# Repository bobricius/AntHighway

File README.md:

# AntHighway
https://hackaday.io/project/164821-ant-highway-linear-motor-for-micro-cars

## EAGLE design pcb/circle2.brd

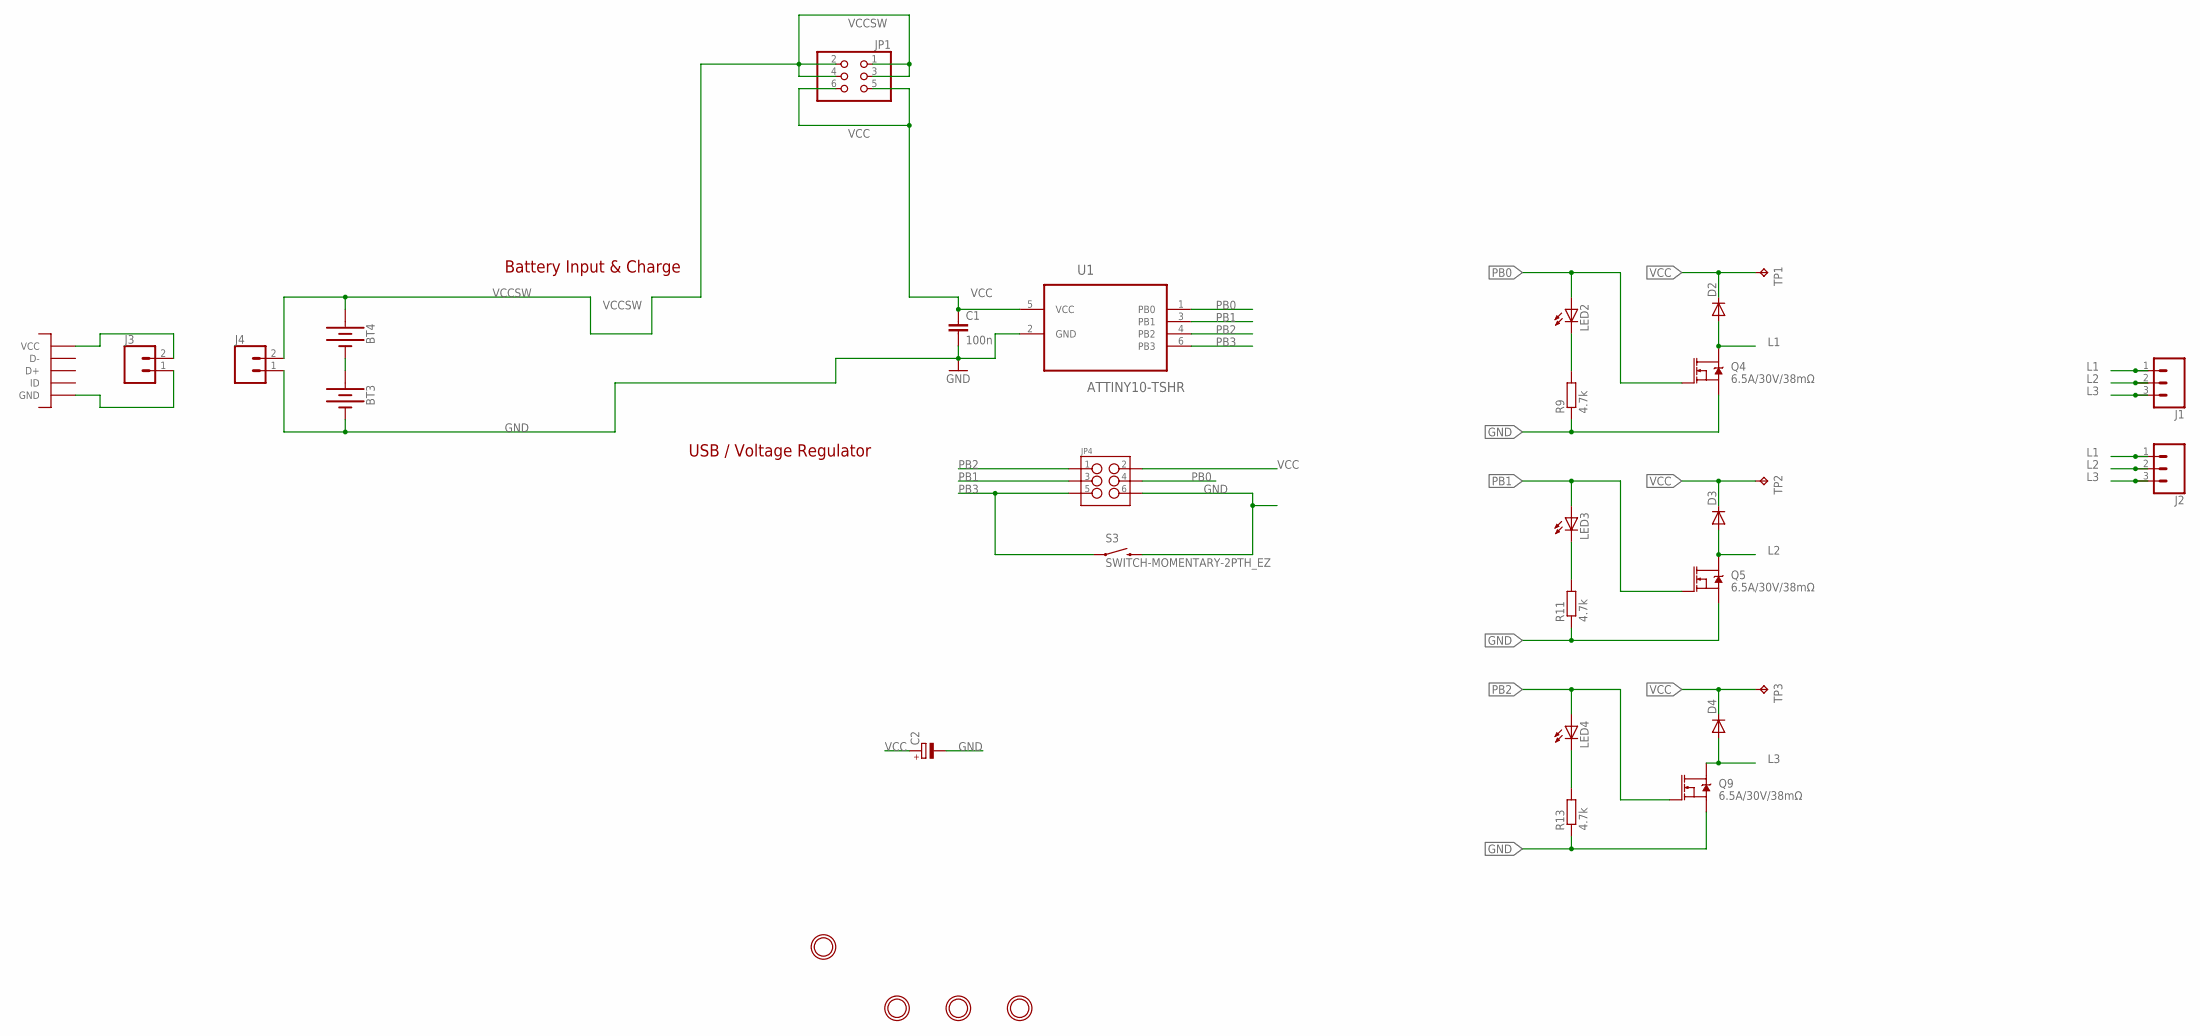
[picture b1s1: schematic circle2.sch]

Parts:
BT3, BT4: BATTERY-AA_KIT; BATTERY-AA-KIT
C1: 100n; 0805
C2: CPOL-EUA; PANASONIC_A
D2, D3, D4: DIODE-DO214AC; DO214AC
J1, J2: CONN_031X03_NO_SILK; 1X03_NO_SILK
J3, J4: CONN_02LOCK_LONGPADS; 1X02_LOCK_LONGPADS
JP1: PINHD-2X3; 2X03
JP4: M03X2NO_SILK; 2X3-NS
LED2, LED3, LED4: LEDKA-3528ASYC; KA-3528ASYC
Q4, Q5, Q9: 6.5A/30V/38mΩ; SO08
R9, R11, R13: 4.7k; R0603
S3: SWITCH-MOMENTARY-2PTH_EZ; TACTILE-PTH-EZ
TP1, TP2, TP3: TPTP20SQ; TP20SQ
U1: ATTINY10-TSHR; SOT95P280X145-6N
U$1, U$2, U$3, U$7: MOUNTINGHOLE2.0; MOUNTINGHOLE_2.0_PLATED
U$5: MICROUSB; MICRO_B

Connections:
GND: BT3.GND@1 (-), C1.2, C2.-, J4.1, JP4.6, Q4.1 (S), Q4.2 (S), Q4.3 (S), Q5.1 (S), Q5.2 (S), Q5.3 (S), Q9.1 (S), Q9.2 (S), Q9.3 (S), R9.1, R11.1, R13.1, S3.3 (2), U1.2 (GND)
GND1: J3.1, U$5.GND1 (GND), U$5.GND2 (GND), U$5.GND3 (GND), U$5.GND4 (GND), U$5.GND7 (GND), U$5.GND8 (GND), U$5.P5 (GND)
L1: D2.A, J1.1, J2.1, Q4.5 (D), Q4.6 (D), Q4.7 (D), Q4.8 (D)
L2: D3.A, J1.2, J2.2, Q5.5 (D), Q5.6 (D), Q5.7 (D), Q5.8 (D)
L3: D4.A, J1.3, J2.3, Q9.5 (D), Q9.6 (D), Q9.7 (D), Q9.8 (D)
unnamed: BT3.PWR@1 (+), BT4.GND@1 (-)
unnamed: LED2.C, R9.2
unnamed: LED3.C, R11.2
unnamed: LED4.C, R13.2
PB0: JP4.4, LED2.A, Q4.4 (G), U1.1 (PB0)
PB1: JP4.3, LED3.A, Q5.4 (G), U1.3 (PB1)
PB2: JP4.1, LED4.A, Q9.4 (G), U1.4 (PB2)
PB3: JP4.5, S3.1, U1.6 (PB3)
VCC: C1.1, C2.+, D2.C, D3.C, D4.C, JP1.5, JP1.6, JP4.2, TP1.TP, TP2.TP, TP3.TP, U1.5 (VCC)
VCC1: J3.2, U$5.P1 (VCC)
VCCSW: BT4.PWR@1 (+), J4.2, JP1.1, JP1.2, JP1.3, JP1.4

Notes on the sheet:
USB / Voltage Regulator
Battery Input & Charge

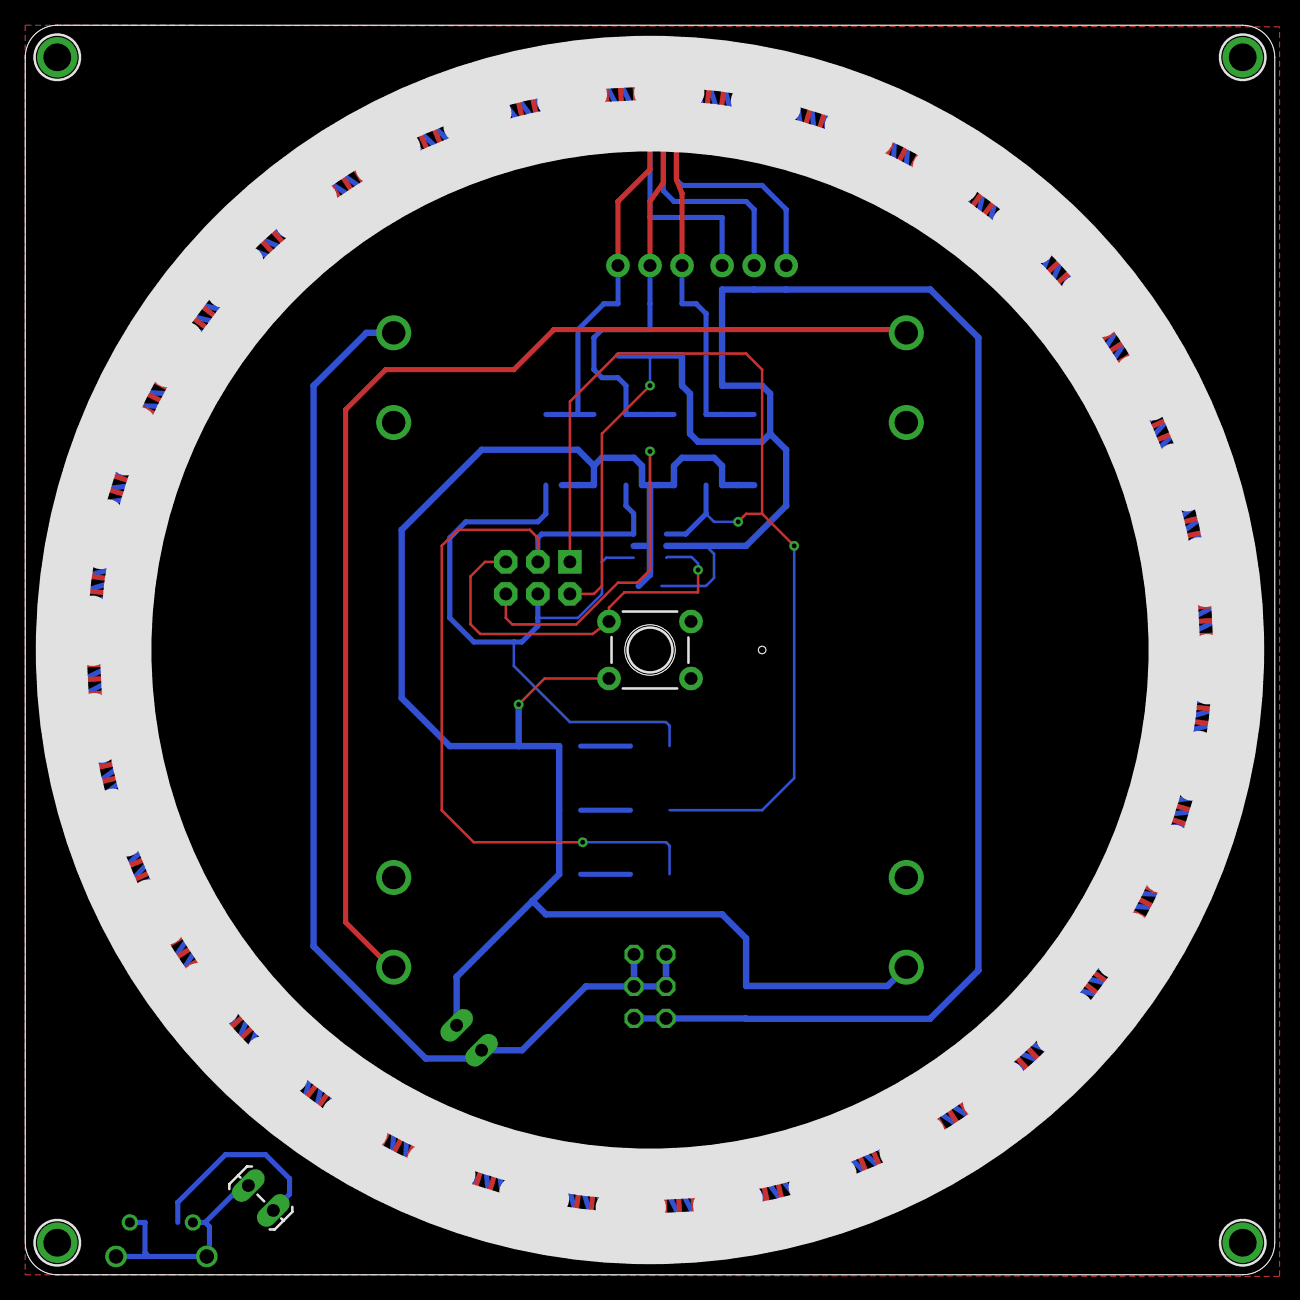
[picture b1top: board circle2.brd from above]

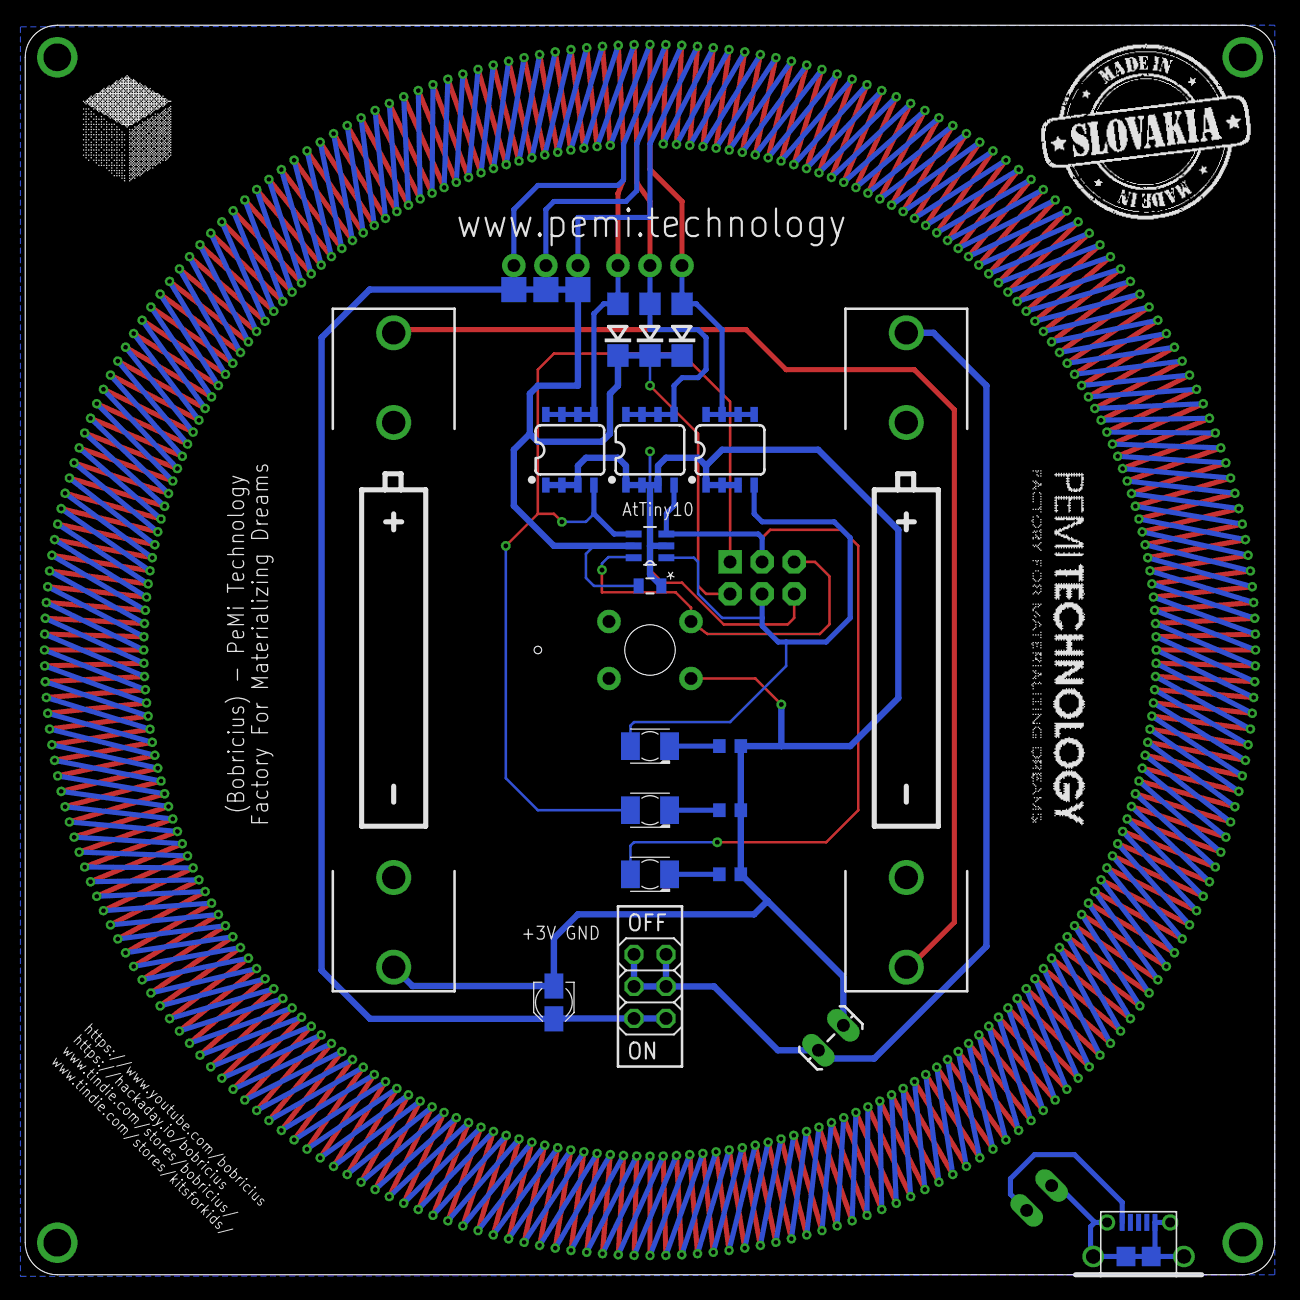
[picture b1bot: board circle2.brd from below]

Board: 2 copper layers, 99.1 x 99.1 mm, 32 parts (23 on the bottom side), 16 nets.

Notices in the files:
parts and their libraries:
SparkFun-Capacitors: Licensing: CC v3.0 Share-Alike You are welcome to use this library for commercial purposes.
SparkFun-Connectors: Licensing: Creative Commons ShareAlike 4.0 International - https://creativecommons.org/licenses/by-sa/4.0
